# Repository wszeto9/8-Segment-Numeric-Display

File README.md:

# 8 Segment Numeric DIsplay

A 10W/digit numeric display to show numbers in any room. Designed for MIT 2.007's Spring gameboard. 

Display showing 2.007

Display showing xx xx

[Interactive BOM for LED Display](https://htmlpreview.github.io/?https://raw.githubusercontent.com/wszeto9/8-Segment-Numeric-Display/main/Documentation/ibom_LED_Panel.html)

[Interactive BOM for LED Display Controller](https://htmlpreview.github.io/?https://raw.githubusercontent.com/wszeto9/8-Segment-Numeric-Display/main/Documentation/ibom_LED_Panel_Controller.html)

[Schematic for LED Display](https://github.com/wszeto9/8-Segment-Numeric-Display/blob/main/Documentation/LED_Panel_Sch.pdf)

[Schematic for LED Display Controller](https://github.com/wszeto9/8-Segment-Numeric-Display/blob/main/Documentation/LED_Panel_Controller_Sch.pdf)

The display is a 65mm x 102mm single layer aluminum PCB. It has a 1x20 SMT male header in order to connect a driver board. The display requires active cooling for duty cycles above 50%. 

The driver is a 75mm x 32mm double layer FR4 PCB. It relies on a 74HC595 shift register to drive a chain of displays using a single data stream. The driving microcontroller can send 3.3V or 5V logic. The logic level is set by the reference voltage on the input. The driver has an onboard buck converter to create the drive voltage of the display. The board can receive 7-28VDC (Peak current draw is 10W/Vin). 
 
# Driving Logic

- Pull nCLR high in order to prevent an accidential clear
- Use SRCLK and SER to send a data packet to the first number's data packet on the right (with LSB first)
- Repeat sending data until all numbers are sent.
- Pulse RCLK to push shifted bits into the outputs
- Use PWM on nOE to adjust the display brightness. Note: The brightness will lower with higher duty cycles.

|Number to display| Data packet|
|--|--|
|0|0b10111011|
|1|0b00000011|
|2|0b00111010|
|3|0b00011110|
|4|0b01000110|
|5|0b01011100|
|6|0b00101110|
|7|0b00110010|
|8|0b01111110|
|9|0b01110010|

# Ordering the LED Panel Parts

From Digikey: quantities are for 1x LED panel.

1x S1113E-20-ND

In addition,

**Red:**

- 20x 90-JE2835ARD-N-0001A0000-N0000001TR-ND

- 10x RMCF2512JT18R0CT-ND

**Blue:**

- 20x  90-JE2835ABL-N-0005A0000-N0000001CT-ND

- 10x 118-CRM2512-JW-6R8ELFCT-ND

**Yellow:**

- 20x 90-JE2835APA-N-0001A0000-N0000001CT-ND
- 10x RMCF2512JT18R0CT-ND

**Green:**
- 20x 90-JE2835AGR-N-0002A0000-N0000001CT-ND
- 10x RMCF2512JT10R0CT-ND

Resistance values for colors:

- Red: For 140mA (25.2lm/led) use 18R
- Amber: For 140mA (24.8lm/led) use 18R
- Green: For 140mA (65.5lm/led) use 10R
- Blue: For 140mA (16.5lm/led) use 6.8R

# Ordering the LED Panel Controller Parts

**Digikey Parts**
|Quantity|Digikey PN| Description|
|--|--|--|
|1|1189-3657-ND|120uF/35V Capacitor|
|1|399-ESK337M016AE3AA-ND|330uF/16V Capacitor|
|1|F3375CT-ND|2A Polyfuse|
|1|455-1849-ND|JST PA 1x04 RA Housing|
|1|455-2753-ND|JST PA 1x04 Connector|
|4|455-1325-1-ND|JST PA Crimp|
|1|1292-WR08X000PTLCT-ND|0805 Jumper|

**Amazon Parts**

- 1x [1x20 female pin socket](https://www.amazon.com/Yohii-Female-Header-2-54mm-Connector/dp/B07P1R9CGT/)

- 1x [LM2596 Buck Converter](https://www.amazon.com/gp/product/B0B63GQDJW/)

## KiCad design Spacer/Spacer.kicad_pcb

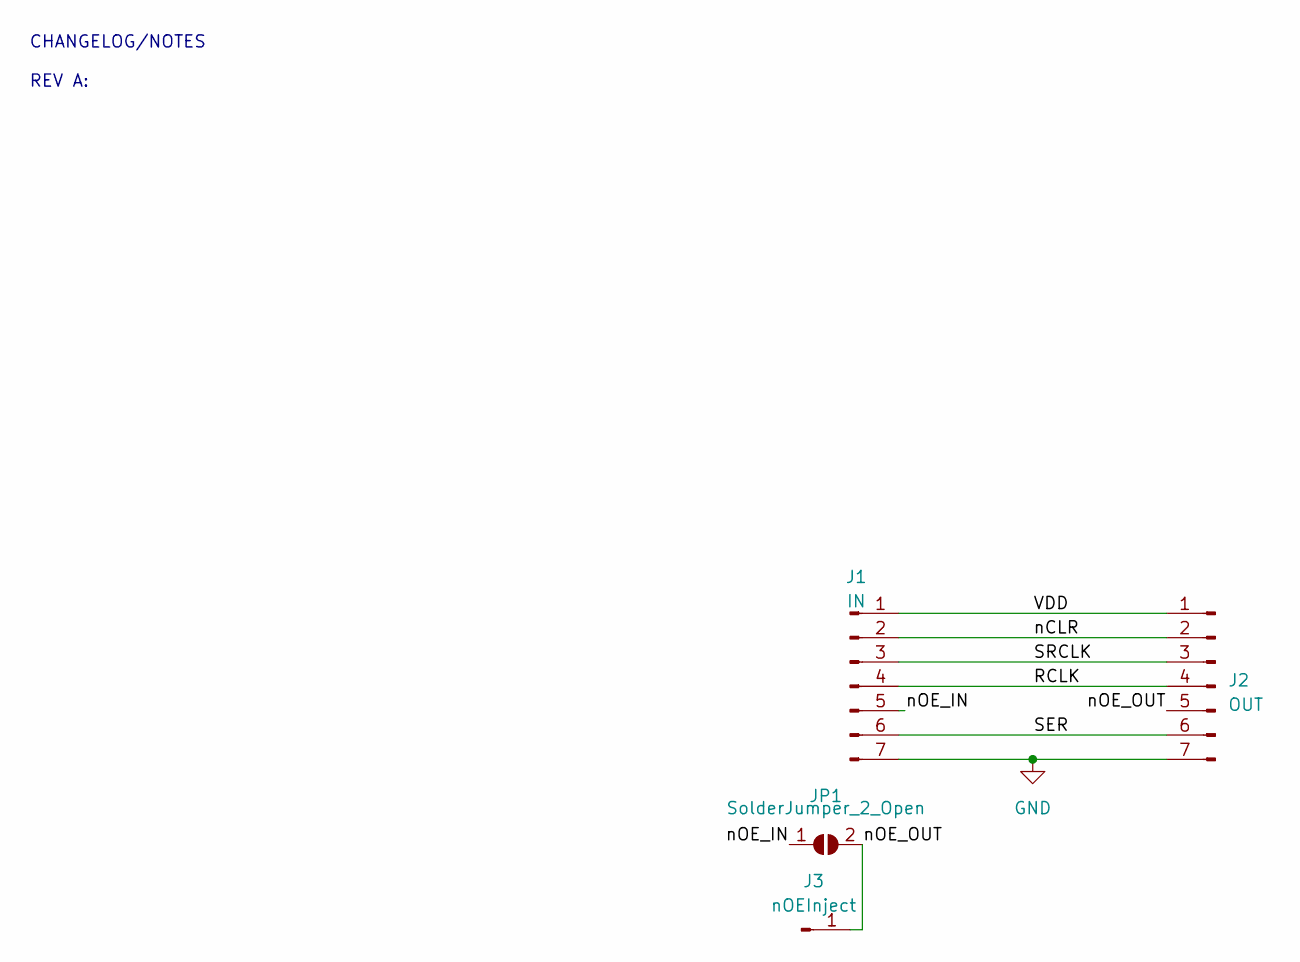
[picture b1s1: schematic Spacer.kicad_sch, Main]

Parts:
J1: IN; PinSocket_1x07_P2.54mm_Horizontal
J2: OUT; PinHeader_1x07_P2.54mm_Horizontal
J3: nOEInject; SolderWire-0.1sqmm_1x01_D0.4mm_OD1mm_Relief2x
JP1: SolderJumper_2_Open; SolderJumper-2_P1.3mm_Open_TrianglePad1.0x1.5mm

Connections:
/RCLK: J1.4, J2.4
/SER: J1.6, J2.6
/SRCLK: J1.3, J2.3
/VDD: J1.1, J2.1
/nCLR: J1.2, J2.2
/nOE_IN: J1.5, JP1.1 (A)
/nOE_OUT: J2.5, J3.1, JP1.2 (B)
GND: J1.7, J2.7

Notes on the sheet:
CHANGELOG/NOTES REV A:

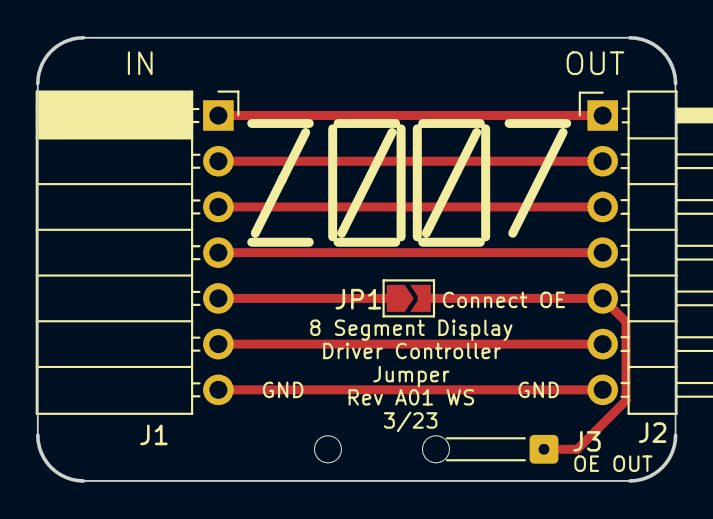
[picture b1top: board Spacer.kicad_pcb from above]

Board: 2 copper layers, 35.4 x 24.6 mm, 4 parts (0 on the bottom side), 8 nets.

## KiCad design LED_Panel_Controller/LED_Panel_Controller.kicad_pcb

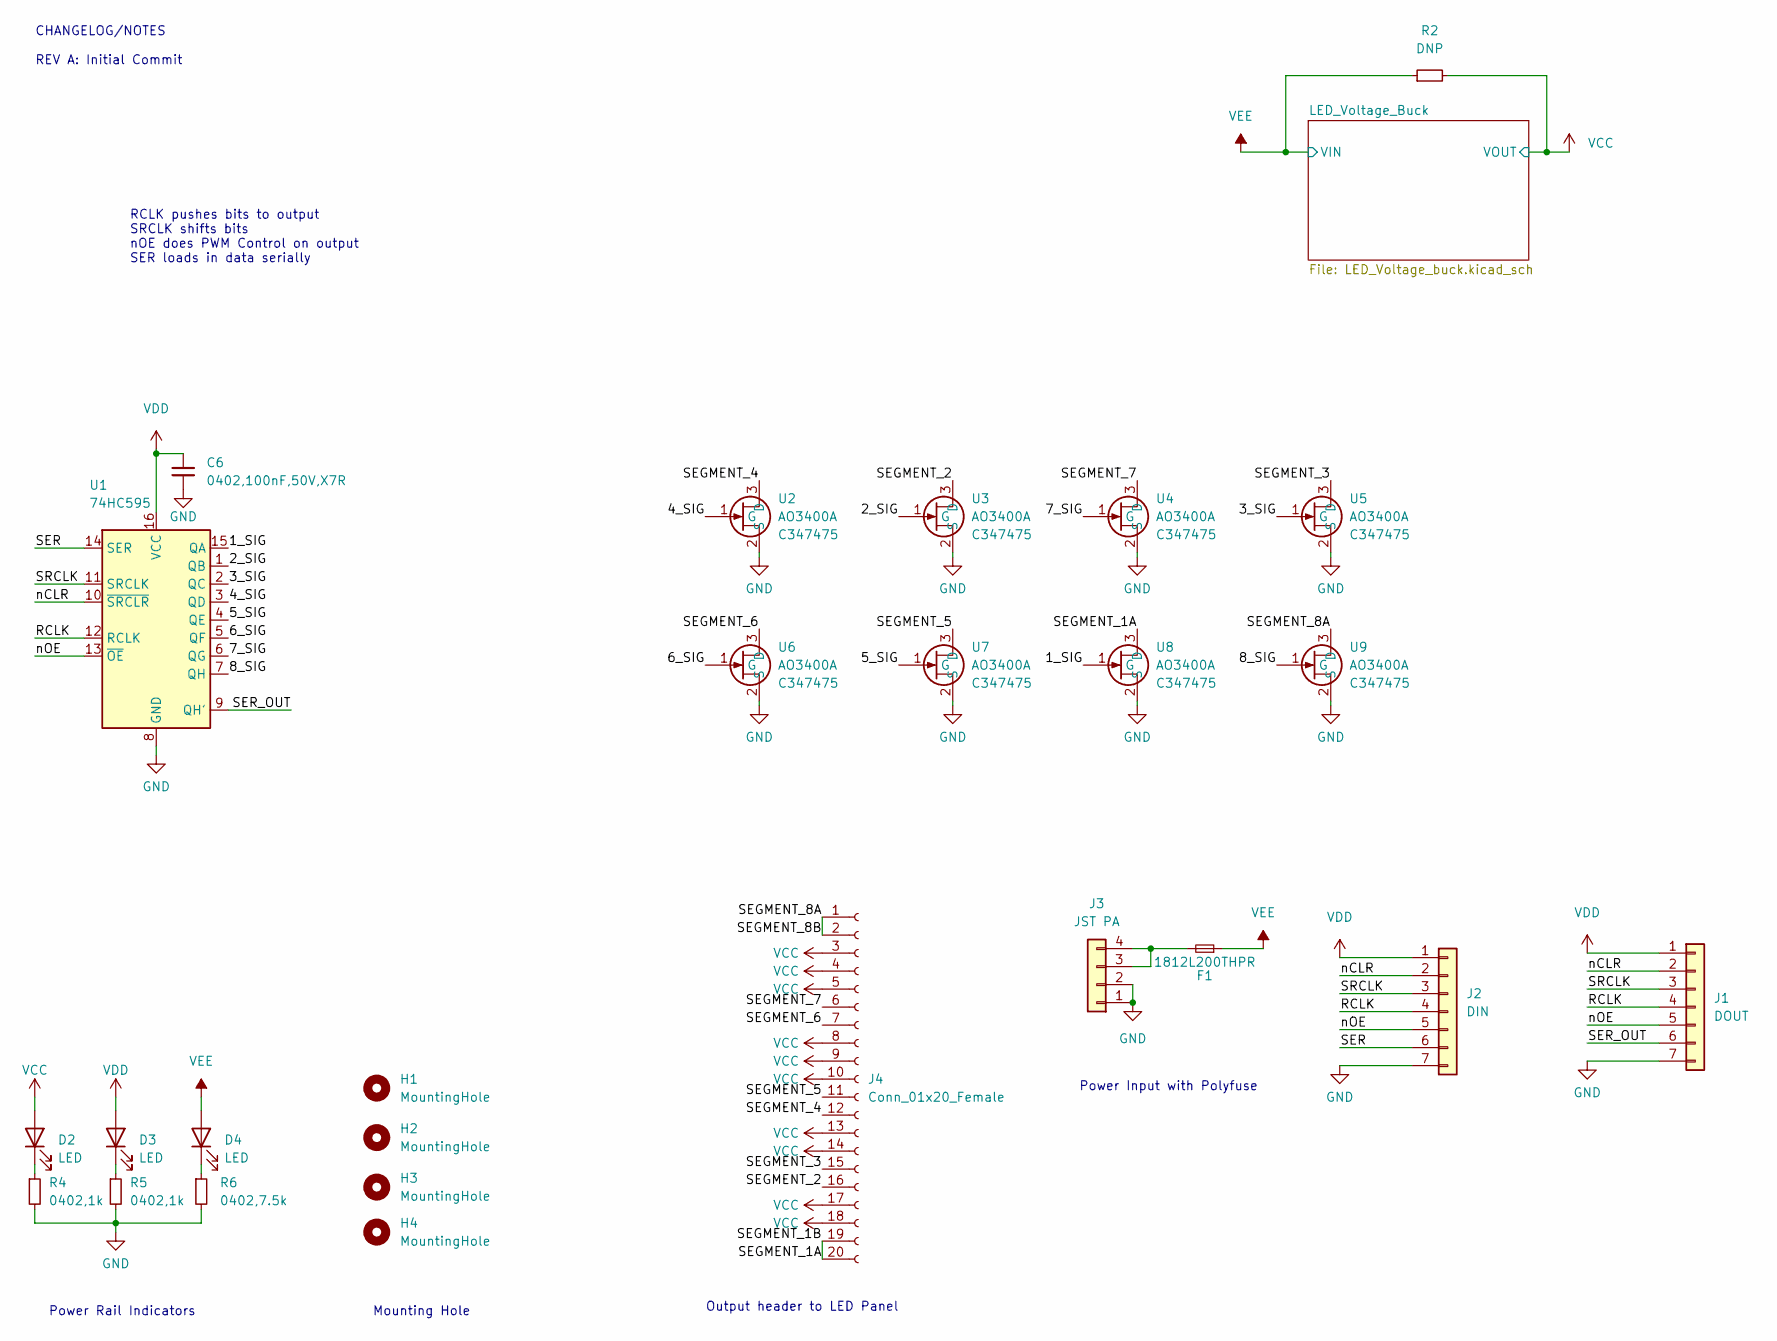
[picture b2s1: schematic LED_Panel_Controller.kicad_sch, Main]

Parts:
C6: 0402,100nF,50V,X7R; C_0402_1005Metric; MFGPN CL05B104KB54PNC; LCSC C307331
D2, D3, D4: LED; LED_0603_1608Metric; LCSC C2290
F1: 3A; Fuse_1812_4532Metric; MFGPN 1812L200THPR; Digikey F3375CT-ND
H1, H2, H3, H4: MountingHole; MountingHole_2.2mm_M2_DIN965_Pad
J1: DOUT; PinHeader_1x07_P2.54mm_Horizontal
J2: DIN; PinSocket_1x07_P2.54mm_Horizontal
J3: JST PA; JST_S04B-PASK-2(LF)(SN); Digikey 455-1849-ND
J4: Conn_01x20_Female; PinSocket_1x20_P2.54mm_Horizontal
R2: DNP; R_0805_2012Metric
R4, R5: 0402,1k; R_0402_1005Metric; MFGPN 0402WGF1001TCE; LCSC C11702
R6: 0402,7.5k; R_0402_1005Metric; MFGPN 0402WGF7501TCE; LCSC C25918
U1: 74HC595; SOIC-16_3.9x9.9mm_P1.27mm; MFGPN CD74HC595M96; LCSC C5947
U2, U3, U4, U5, U6, U7, U8, U9: AO3400A; SOT-23; LCSC C347475

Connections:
/1_SIG: U1.15 (QA), U8.1 (G)
/2_SIG: U1.1 (QB), U3.1 (G)
/3_SIG: U1.2 (QC), U5.1 (G)
/4_SIG: U1.3 (QD), U2.1 (G)
/5_SIG: U1.4 (QE), U7.1 (G)
/6_SIG: U1.5 (QF), U6.1 (G)
/7_SIG: U1.6 (QG), U4.1 (G)
/8_SIG: U1.7 (QH), U9.1 (G)
/RCLK: J1.4, J2.4, U1.12 (RCLK)
/SEGMENT_1A: J4.19, J4.20, U8.3 (D)
/SEGMENT_2: J4.16, U3.3 (D)
/SEGMENT_3: J4.15, U5.3 (D)
/SEGMENT_4: J4.12, U2.3 (D)
/SEGMENT_5: J4.11, U7.3 (D)
/SEGMENT_6: J4.7, U6.3 (D)
/SEGMENT_7: J4.6, U4.3 (D)
/SEGMENT_8A: J4.1, J4.2, U9.3 (D)
/SER: J2.6, U1.14 (SER)
/SER_OUT: J1.6, U1.9 (QH')
/SRCLK: J1.3, J2.3, U1.11 (SRCLK)
/nCLR: J1.2, J2.2, U1.10 (~SRCLR)
/nOE: J1.5, J2.5, U1.13 (~OE)
GND: C6.2, J1.7, J2.7, J3.1, J3.2, R4.2, R5.2, R6.2, U1.8 (GND), U2.2 (S), U3.2 (S), U4.2 (S), U5.2 (S), U6.2 (S), U7.2 (S), U8.2 (S), U9.2 (S); also elsewhere on the board
unnamed: D2.1 (K), R4.1
unnamed: D3.1 (K), R5.1
unnamed: D4.1 (K), R6.1
unnamed: F1.2, J3.3, J3.4
VCC: D2.2 (A), J4.3, J4.4, J4.5, J4.8, J4.9, J4.10, J4.13, J4.14, J4.17, J4.18, R2.2; also elsewhere on the board
VDD: C6.1, D3.2 (A), J1.1, J2.1, U1.16 (VCC)
VEE: D4.2 (A), F1.1, R2.1; also elsewhere on the board

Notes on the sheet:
Power Input with Polyfuse
RCLK pushes bits to output SRCLK shifts bits nOE does PWM Control on output SER loads in data serially
Mounting Hole
Output header to LED Panel
Power Rail Indicators
CHANGELOG/NOTES REV A: Initial Commit

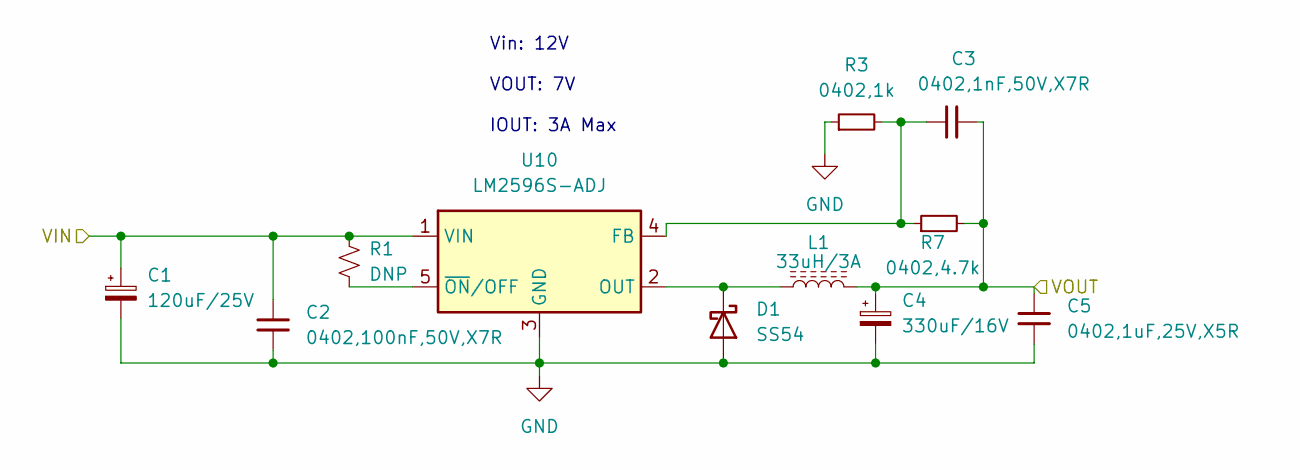
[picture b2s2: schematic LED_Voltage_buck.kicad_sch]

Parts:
C1: 120uF/25V; C_Radial_D6.3mm_H11.0mm_P2.50mm; MFGPN 860010473009; Digikey 732-8632-1-ND
C2: 0402,100nF,50V,X7R; C_0402_1005Metric; MFGPN CL05B104KB54PNC; LCSC C307331
C3: 0402,1nF,50V,X7R; C_0402_1005Metric; MFGPN 0402B102K500NT; LCSC C1523
C4: 330uF/16V; C_Radial_D6.3mm_H11.0mm_P2.50mm; MFGPN 860020373011; Digikey 732-8798-1-ND
C5: 0402,1uF,25V,X5R; C_0402_1005Metric; MFGPN CL05A105KA5NQNC; LCSC C52923
D1: SS54; D_SMA; LCSC C22452
L1: 33uH/3A; L_10.4x10.4_H4.8; LCSC C225031
R1: DNP; R_0402_1005Metric
R3: 0402,1k; R_0402_1005Metric; MFGPN 0402WGF1001TCE; LCSC C11702
R7: 0402,4.7k; R_0402_1005Metric; MFGPN 0402WGF4701TCE; LCSC C25900
U10: LM2596S-ADJ; TO-263-5_TabPin3; MFGPN LM2596S-ADJ

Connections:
GND: C1.2, C2.2, C4.2, C5.2, D1.2 (A), R3.1, U10.3 (GND); also elsewhere on the board
unnamed: C3.1, R3.2, R7.1, U10.4 (FB)
unnamed: D1.1 (K), L1.1, U10.2 (OUT)
unnamed: R1.1, U10.5 (~ON/OFF)
VCC: C3.2, C4.1, C5.1, L1.2, R7.2; also elsewhere on the board
VEE: C1.1, C2.1, R1.2, U10.1 (VIN); also elsewhere on the board

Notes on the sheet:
Vin: 12V VOUT: 7V IOUT: 3A Max

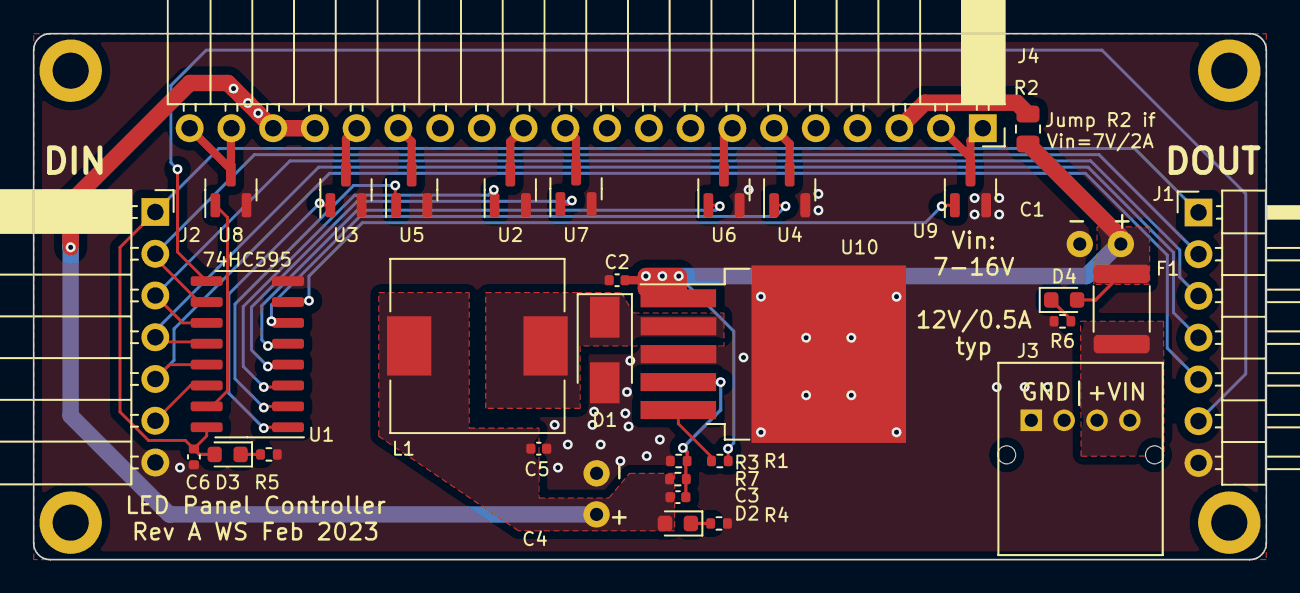
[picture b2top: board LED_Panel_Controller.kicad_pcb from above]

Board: 2 copper layers, 75.0 x 32.0 mm, 37 parts (0 on the bottom side), 33 nets.

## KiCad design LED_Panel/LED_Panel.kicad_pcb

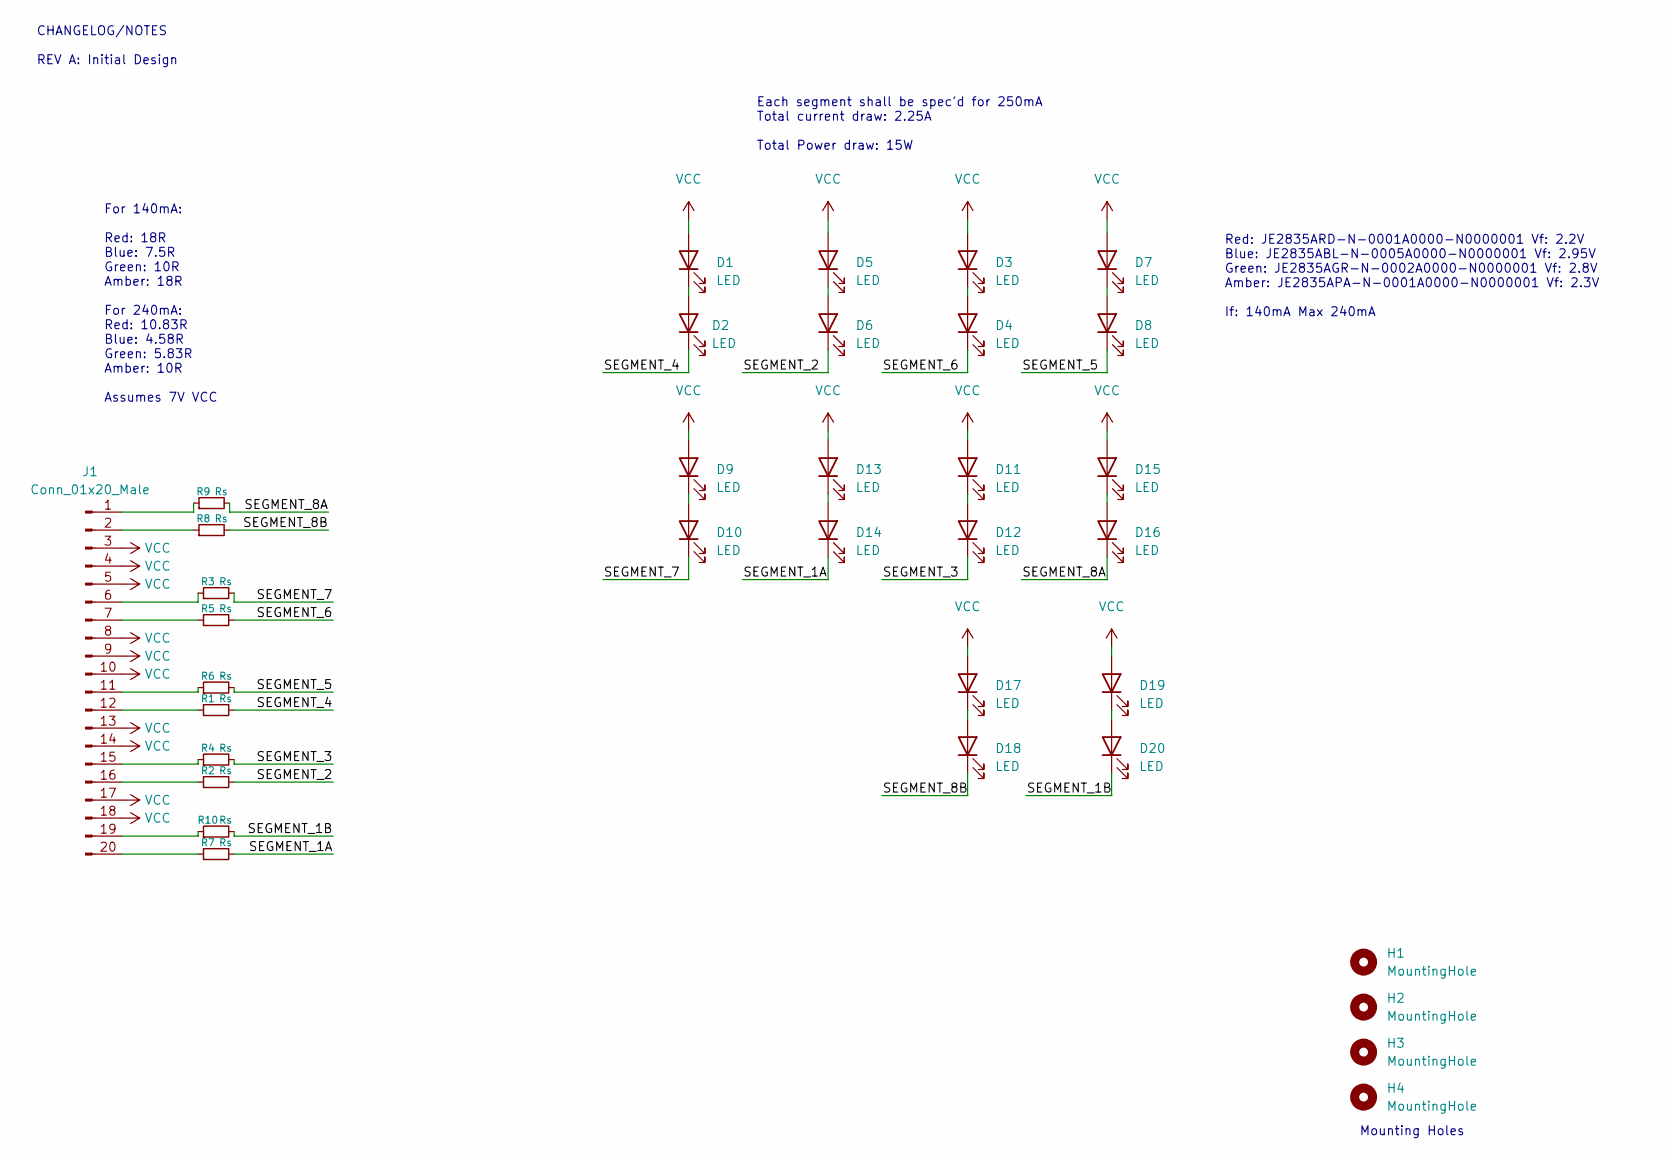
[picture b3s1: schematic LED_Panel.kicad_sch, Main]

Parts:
D1, D2, D3, D4, D5, D6, D7, D8, D9, D10, D11, D12, D13, D14, D15, D16, D17, D18, D19, D20: LED; LED_PLCC_2835
H1, H2, H3, H4: MountingHole; MountingHole_3.2mm_M3_DIN965_Pad
J1: Conn_01x20_Male; Harwin_M20-89020xx_1x20_P2.54mm_Horizontal; Digikey S1113E-20-ND
R1, R2, R3, R4, R5, R6, R7, R8, R9, R10: Rs; R_2512_6332Metric

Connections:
/SEGMENT_1A: D14.1 (K), R7.2
/SEGMENT_1B: D20.1 (K), R10.2
/SEGMENT_2: D6.1 (K), R2.2
/SEGMENT_3: D12.1 (K), R4.2
/SEGMENT_4: D2.1 (K), R1.2
/SEGMENT_5: D8.1 (K), R6.2
/SEGMENT_6: D4.1 (K), R5.2
/SEGMENT_7: D10.1 (K), R3.2
/SEGMENT_8A: D16.1 (K), R9.2
/SEGMENT_8B: D18.1 (K), R8.2
unnamed: D1.1 (K), D2.2 (A)
unnamed: D3.1 (K), D4.2 (A)
unnamed: D5.1 (K), D6.2 (A)
unnamed: D7.1 (K), D8.2 (A)
unnamed: D9.1 (K), D10.2 (A)
unnamed: D11.1 (K), D12.2 (A)
unnamed: D13.1 (K), D14.2 (A)
unnamed: D15.1 (K), D16.2 (A)
unnamed: D17.1 (K), D18.2 (A)
unnamed: D19.1 (K), D20.2 (A)
unnamed: J1.1, R9.1
unnamed: J1.2, R8.1
unnamed: J1.6, R3.1
unnamed: J1.7, R5.1
unnamed: J1.11, R6.1
unnamed: J1.12, R1.1
unnamed: J1.15, R4.1
unnamed: J1.16, R2.1
unnamed: J1.19, R10.1
unnamed: J1.20, R7.1
VCC: D1.2 (A), D3.2 (A), D5.2 (A), D7.2 (A), D9.2 (A), D11.2 (A), D13.2 (A), D15.2 (A), D17.2 (A), D19.2 (A), J1.3, J1.4, J1.5, J1.8, J1.9, J1.10, J1.13, J1.14, J1.17, J1.18

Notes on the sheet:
Mounting Holes
Red: JE2835ARD-N-0001A0000-N0000001 Vf: 2.2V Blue: JE2835ABL-N-0005A0000-N0000001 Vf: 2.95V Green: JE2835AGR-N-0002A0000-N0000001 Vf: 2.8V Amber: JE2835APA-N-0001A0000-N0000001 Vf: 2.3V If: 140mA Max 240mA
Each segment shall be spec'd for 250mA Total current draw: 2.25A Total Power draw: 15W
For 140mA: Red: 18R Blue: 7.5R Green: 10R Amber: 18R For 240mA: Red: 10.83R Blue: 4.58R Green: 5.83R Amber: 10R Assumes 7V VCC
CHANGELOG/NOTES REV A: Initial Design

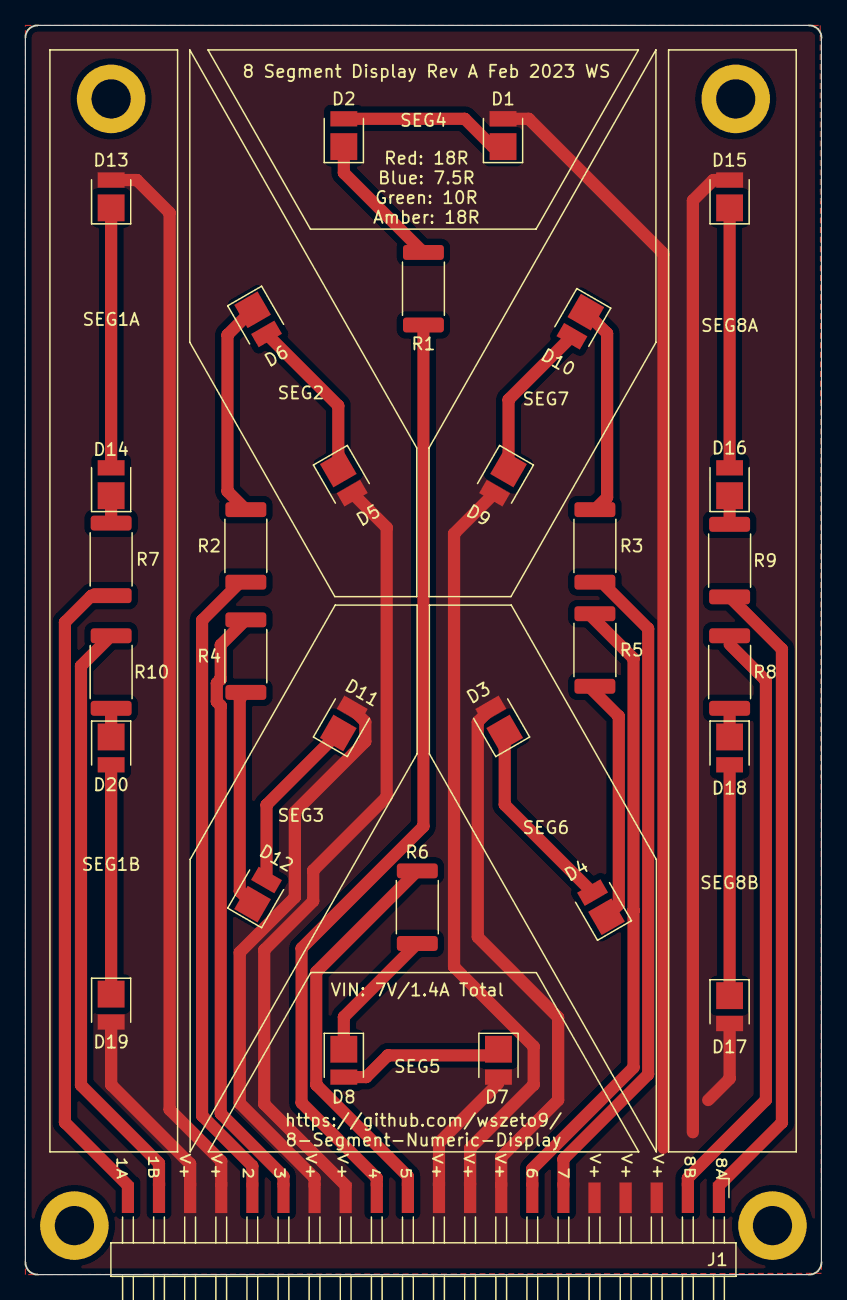
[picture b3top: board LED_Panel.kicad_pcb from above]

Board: 2 copper layers, 65.0 x 102.0 mm, 35 parts (0 on the bottom side), 31 nets.

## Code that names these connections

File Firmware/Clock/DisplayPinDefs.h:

#define SER 16
#define nOE 18
#define RCLK 33
#define SRCLK 35
#define nCLR 37
#define DISPLAYVDD 39

uint8_t displayData[] ={ 
0b10111011,
0b00000011,
0b00111010,
0b00011110,
0b01000110,
0b01011100,
0b00101110,
0b00110010,
0b01111110,
0b01011110
};

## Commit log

2023-02-08 Added STEP files
2023-02-08 changed 1x20 header digikey PN
2023-02-08 Added documentation
2023-02-08 renamed gerber files for LED panel
2023-02-08 edited header PN
2023-02-08 renamed and moved led panel iBOM
2023-02-08 updated gerber names
2023-02-08 updated BOM
2023-02-08 changed page size, BOM
2023-02-08 updated documentation
2023-02-09 changed VIN cap to 35V rating
2023-02-09 updated readme to use 35V capacitor PN
2023-02-09 corrected resistor PNs
2023-03-14 added images
2023-03-14 added firmware for arduino
2023-03-14 maximum voltage changed to 28V
2023-03-30 Changed FW to work with servos
2023-03-30 Created a spacer PCB
2023-07-19 updated silk
2024-06-08 added firmware to use the display as a clock
